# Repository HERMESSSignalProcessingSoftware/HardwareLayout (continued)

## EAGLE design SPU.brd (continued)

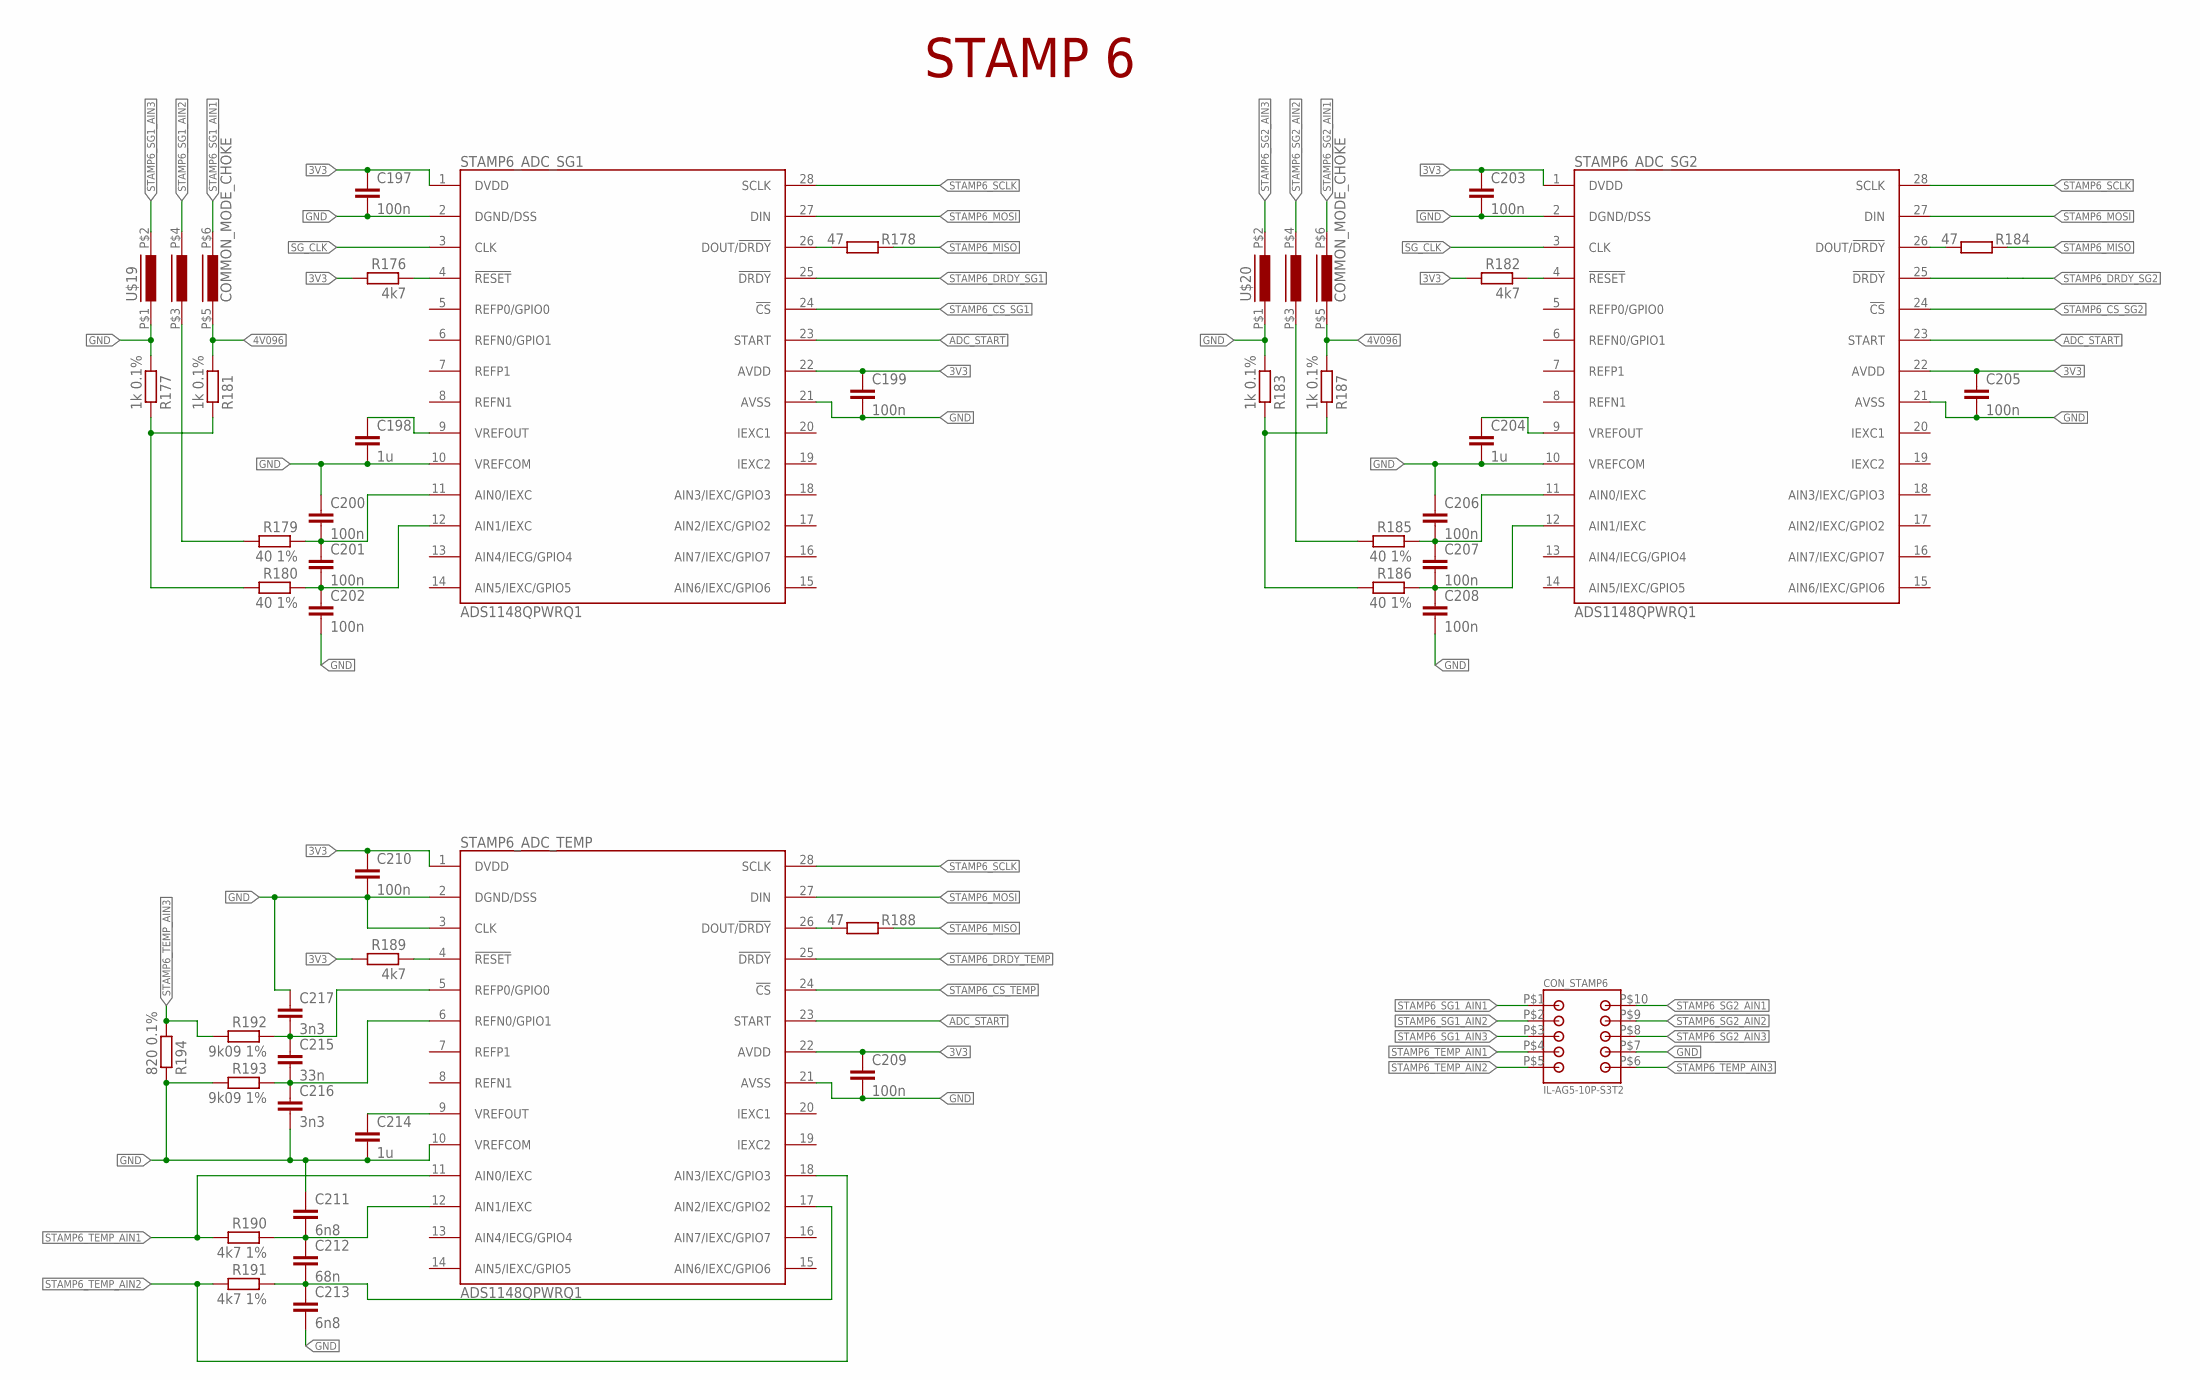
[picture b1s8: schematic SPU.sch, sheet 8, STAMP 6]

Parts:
C197, C199, C200, C201, C202, C203, C205, C206, C207, C208, C209, C210: 100n; C0805
C198, C204, C214: 1u; C0805
C211, C213: 6n8; C0805
C212: 68n; C0805
C215: 33n; C0805
C216, C217: 3n3; C0805
CON_STAMP6: IL-AG5-10P-S3T2
R176, R182, R189: 4k7; R0805
R177, R181, R183, R187: 1k 0.1%; R0805
R178, R184, R188: 47; R0805
R179, R180, R185, R186: 40 1%; R0805
R190, R191: 4k7 1%; R0805
R192, R193: 9k09 1%; R0805
R194: 820 0.1%; R0805
STAMP6_ADC_SG1, STAMP6_ADC_SG2, STAMP6_ADC_TEMP: ADS1148QPWRQ1; TSSOP28
U$19, U$20: COMMON_MODE_CHOKE

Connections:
3V3: C197.1, C199.1, C203.1, C205.1, C209.1, C210.1, R176.2, R182.2, R189.2, STAMP6_ADC_SG1.1 (DVDD), STAMP6_ADC_SG1.22 (AVDD), STAMP6_ADC_SG2.1 (DVDD), STAMP6_ADC_SG2.22 (AVDD), STAMP6_ADC_TEMP.1 (DVDD), STAMP6_ADC_TEMP.22 (AVDD); also elsewhere on the board
4V096: R181.2, R187.2, U$19.P$5 (5), U$20.P$5 (5); also elsewhere on the board
ADC_START: STAMP6_ADC_SG1.23 (START), STAMP6_ADC_SG2.23 (START), STAMP6_ADC_TEMP.23 (START); also elsewhere on the board
GND: C197.2, C198.2, C199.2, C200.1, C202.2, C203.2, C204.2, C205.2, C206.1, C208.2, C209.2, C210.2, C211.1, C213.2, C214.2, C216.2, C217.1, CON_STAMP6.P$7, R177.2, R183.2, R193.2, R194.1, STAMP6_ADC_SG1.2 (DGND/DSS), STAMP6_ADC_SG1.10 (VREFCOM), STAMP6_ADC_SG1.21 (AVSS), STAMP6_ADC_SG2.2 (DGND/DSS), STAMP6_ADC_SG2.10 (VREFCOM), STAMP6_ADC_SG2.21 (AVSS), STAMP6_ADC_TEMP.2 (DGND/DSS), STAMP6_ADC_TEMP.3 (CLK), STAMP6_ADC_TEMP.10 (VREFCOM), STAMP6_ADC_TEMP.21 (AVSS), U$19.P$1 (1), U$20.P$1 (1); also elsewhere on the board
unnamed: R176.1, STAMP6_ADC_SG1.4 (!RESET)
unnamed: C198.1, STAMP6_ADC_SG1.9 (VREFOUT)
unnamed: R178.2, STAMP6_ADC_SG1.26 (DOUT/!DRDY)
unnamed: C200.2, C201.1, R179.1, STAMP6_ADC_SG1.11 (AIN0/IEXC)
unnamed: C201.2, C202.1, R180.1, STAMP6_ADC_SG1.12 (AIN1/IEXC)
unnamed: R177.1, R180.2, R181.1
unnamed: R179.2, U$19.P$3 (3)
unnamed: R182.1, STAMP6_ADC_SG2.4 (!RESET)
unnamed: C204.1, STAMP6_ADC_SG2.9 (VREFOUT)
unnamed: R184.2, STAMP6_ADC_SG2.26 (DOUT/!DRDY)
unnamed: C206.2, C207.1, R185.1, STAMP6_ADC_SG2.11 (AIN0/IEXC)
unnamed: C207.2, C208.1, R186.1, STAMP6_ADC_SG2.12 (AIN1/IEXC)
unnamed: R183.1, R186.2, R187.1
unnamed: R185.2, U$20.P$3 (3)
unnamed: R188.2, STAMP6_ADC_TEMP.26 (DOUT/!DRDY)
unnamed: R189.1, STAMP6_ADC_TEMP.4 (!RESET)
unnamed: C211.2, C212.1, R190.1, STAMP6_ADC_TEMP.12 (AIN1/IEXC)
unnamed: C212.2, C213.1, R191.1, STAMP6_ADC_TEMP.17 (AIN2/IEXC/GPIO2)
unnamed: C214.1, STAMP6_ADC_TEMP.9 (VREFOUT)
unnamed: C215.2, C216.1, R193.1, STAMP6_ADC_TEMP.6 (REFN0/GPIO1)
unnamed: C215.1, C217.2, R192.1, STAMP6_ADC_TEMP.5 (REFP0/GPIO0)
SG_CLK: STAMP6_ADC_SG1.3 (CLK), STAMP6_ADC_SG2.3 (CLK); also elsewhere on the board
STAMP6_CS_SG1: STAMP6_ADC_SG1.24 (!CS); also elsewhere on the board
STAMP6_CS_SG2: STAMP6_ADC_SG2.24 (!CS); also elsewhere on the board
STAMP6_CS_TEMP: STAMP6_ADC_TEMP.24 (!CS); also elsewhere on the board
STAMP6_DRDY_SG1: STAMP6_ADC_SG1.25 (!DRDY); also elsewhere on the board
STAMP6_DRDY_SG2: STAMP6_ADC_SG2.25 (!DRDY); also elsewhere on the board
STAMP6_DRDY_TEMP: STAMP6_ADC_TEMP.25 (!DRDY); also elsewhere on the board
STAMP6_MISO: R178.1, R184.1, R188.1; also elsewhere on the board
STAMP6_MOSI: STAMP6_ADC_SG1.27 (DIN), STAMP6_ADC_SG2.27 (DIN), STAMP6_ADC_TEMP.27 (DIN); also elsewhere on the board
STAMP6_SCLK: STAMP6_ADC_SG1.28 (SCLK), STAMP6_ADC_SG2.28 (SCLK), STAMP6_ADC_TEMP.28 (SCLK); also elsewhere on the board
STAMP6_SG1_AIN1: CON_STAMP6.P$1, U$19.P$6 (6)
STAMP6_SG1_AIN2: CON_STAMP6.P$2, U$19.P$4 (4)
STAMP6_SG1_AIN3: CON_STAMP6.P$3, U$19.P$2 (2)
STAMP6_SG2_AIN1: CON_STAMP6.P$10, U$20.P$6 (6)
STAMP6_SG2_AIN2: CON_STAMP6.P$9, U$20.P$4 (4)
STAMP6_SG2_AIN3: CON_STAMP6.P$8, U$20.P$2 (2)
STAMP6_TEMP_AIN1: CON_STAMP6.P$4, R190.2, STAMP6_ADC_TEMP.11 (AIN0/IEXC)
STAMP6_TEMP_AIN2: CON_STAMP6.P$5, R191.2, STAMP6_ADC_TEMP.18 (AIN3/IEXC/GPIO3)
STAMP6_TEMP_AIN3: CON_STAMP6.P$6, R192.2, R194.2

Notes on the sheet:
STAMP 6

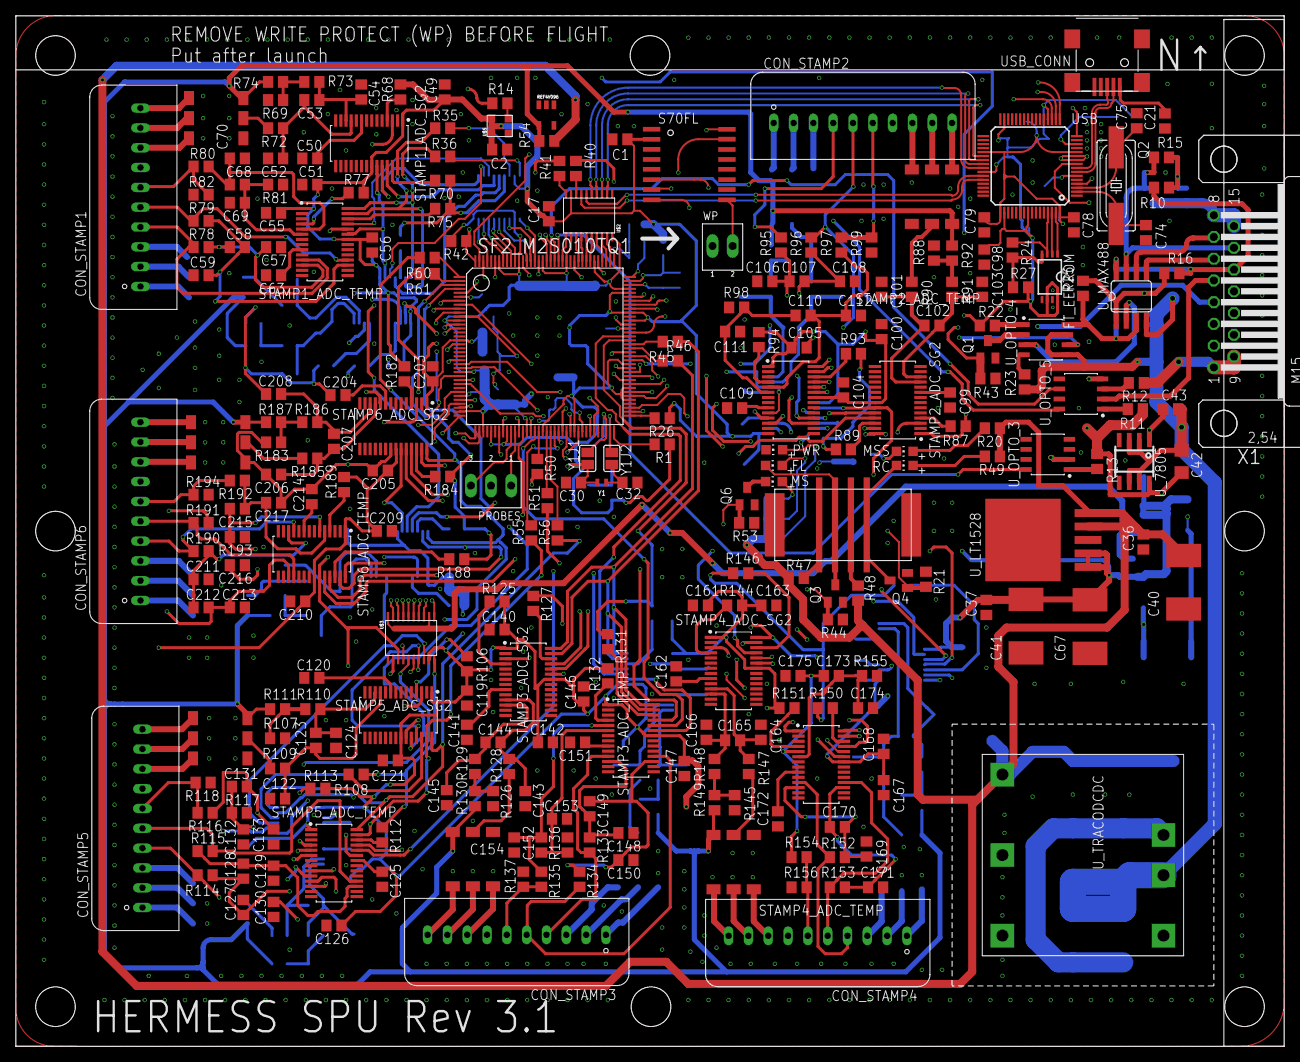
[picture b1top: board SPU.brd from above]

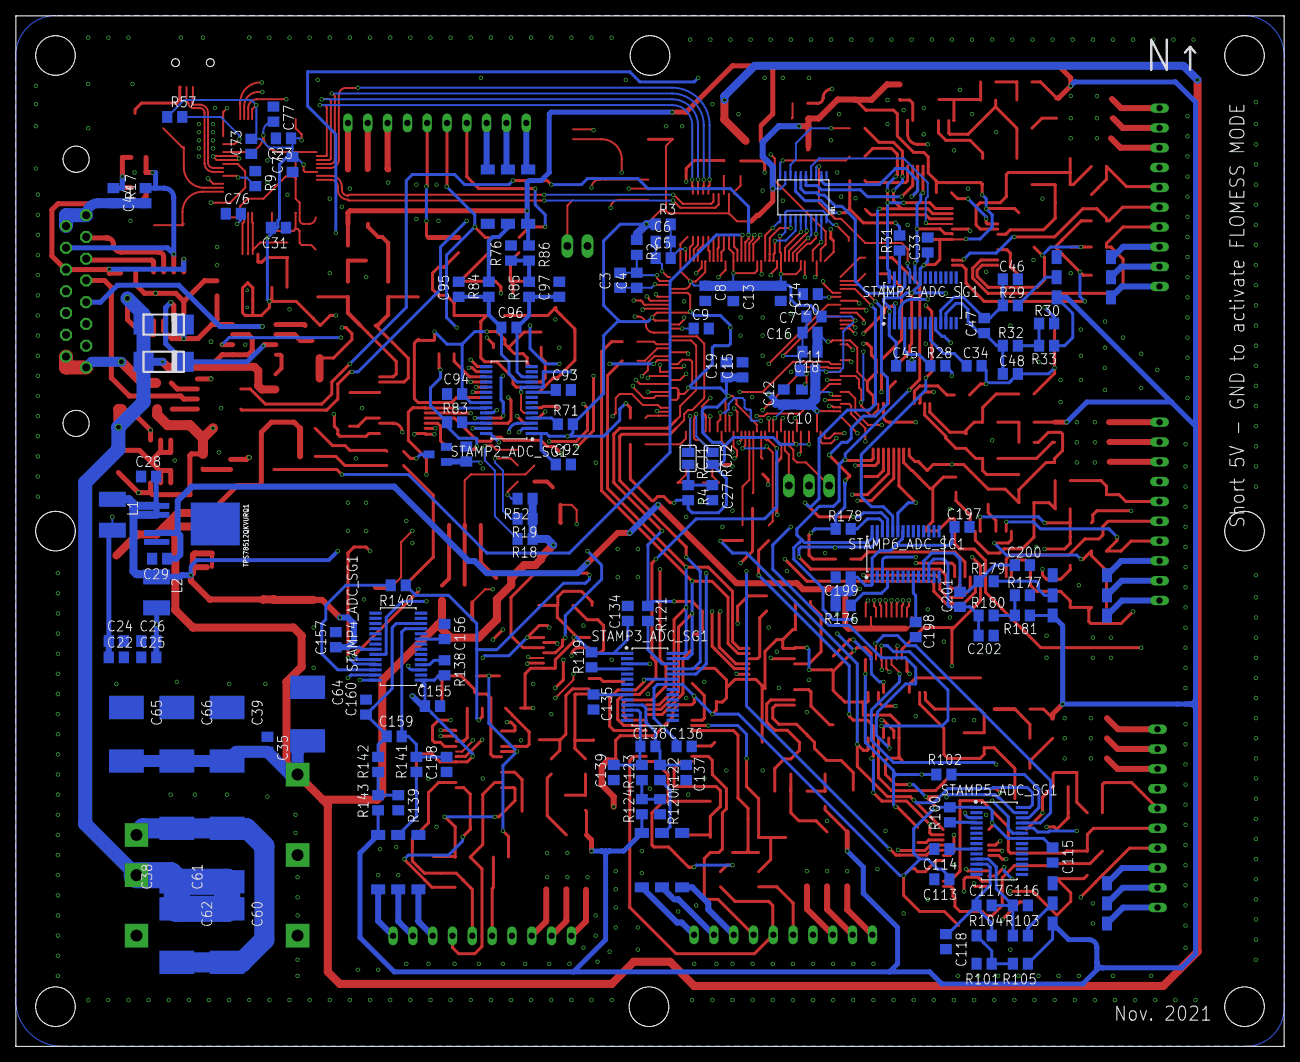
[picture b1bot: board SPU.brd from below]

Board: 4 copper layers, 160.0 x 130.0 mm, 421 parts (143 on the bottom side), 360 nets.

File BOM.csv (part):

"Qty";"Value";"Device";"Package";"Parts";"Description";"CATEGORY";"DESCRIPTION";"HEAT-SINK";"MANUFACTURER";"MF";"MPN";"OC_FARNELL";"OC_NEWARK";"OPERATING_TEMP";"OPERTAING_TEMP";"PART_STATUS";"POPULARITY";"ROHS_COMPLIANT";"SERIES";"SPICEPREFIX";"SUB-CATEGORY";"THERMALLOSS";"TYPE";"VALUE";
"2";"";"L-EUL1812";"L1812";"L1, L2";"INDUCTOR, European symbol";"";"";"";"";"";"";"";"";"";"";"";"18";"";"";"L";"";"";"";"";
"1";"";"M15H";"M15H";"X1";"SUB-D";"";"";"";"";"";"";"unknown";"unknown";"";"";"";"0";"";"";"";"";"";"";"";
"1";"";"PSS254_G2";"PSS254_G2";"WP";"";"";"";"";"";"";"";"";"";"";"";"";"";"";"";"";"";"";"";"";
"1";"";"PSS254_G3";"PSS254_G3";"PROBES";"";"";"";"";"";"";"";"";"";"";"";"";"";"";"";"";"";"";"";"";
"1";"";"USBMINIB";"USB-MINIB";"CN1";"USB Connectors";"";"";"";"";"";"";"";"";"";"";"";"";"";"";"";"";"";"";"";
"103";"100n";"C-EUC0805";"C0805";"C1, C7, C8, C9, C10, C11, C12, C13, C14, C15, C16, C17, C18, C19, C20, C21, C22, C23, C25, C28, C29, C30, C31, C32, C33, C35, C36, C37, C43, C45, C46, C47, C48, C49, C51, C52, C53, C54, C55, C56, C71, C72, C73, C92, C94, C95, C96, C97, C98, C100, C101, C102, C103, C104, C105, C113, C115, C116, C117, C118, C119, C121, C122, C123, C124, C125, C126, C134, C136, C137, C138, C139, C140, C142, C143, C144, C145, C146, C147, C155, C157, C158, C159, C160, C161, C163, C164, C165, C166, C167, C168, C197, C199, C200, C201, C202, C203, C205, C206, C207, C208, C209, C210";"CAPACITOR, European symbol";"";"";"";"";"";"";"";"";"";"";"";"88";"";"";"C";"";"";"";"";
"1";"100n";"C-EUC1206";"C1206";"C42";"CAPACITOR, European symbol";"";"";"";"";"";"";"";"";"";"";"";"54";"";"";"C";"";"";"";"";
"3";"10k";"R-EU_R0805";"R0805";"R1, R26, R27";"RESISTOR, European symbol";"";"";"";"";"";"";"";"";"";"";"";"86";"";"";"R";"";"";"";"";
"1";"10n";"C-EUC0805";"C0805";"C2";"CAPACITOR, European symbol";"";"";"";"";"";"";"";"";"";"";"";"88";"";"";"C";"";"";"";"";
"11";"10u";"CPOL-EUE/7260-38W";"E/7260-38W";"C38, C39, C40, C41, C60, C61, C62, C64, C65, C66, C67";"POLARIZED CAPACITOR, European symbol";"";"";"";"";"";"";"";"";"";"";"";"0";"";"";"C";"";"";"";"";
"1";"12MHz";"CRYSTALHC49UP";"HC49UP";"Q2";"CRYSTAL";"";"";"";"";"";"";"unknown";"unknown";"";"";"";"";"";"";"";"";"";"";"";
"1";"12k";"R-EU_R0805";"R0805";"R9";"RESISTOR, European symbol";"";"";"";"";"";"";"";"";"";"";"";"86";"";"";"R";"";"";"";"";
"1";"150n";"C-EUC0805";"C0805";"C27";"CAPACITOR, European symbol";"";"";"";"";"";"";"";"";"";"";"";"88";"";"";"C";"";"";"";"";
"5";"1V9";"LEDCHIP-LED0805";"CHIP-LED0805";"LED1, LED2, LED3, LED4, LED5";"LED";"";"";"";"";"";"";"";"";"";"";"";"";"";"";"";"";"";"";"";
"1";"1k";"R-EU_R0805";"R0805";"R57";"RESISTOR, European symbol";"";"";"";"";"";"";"";"";"";"";"";"86";"";"";"R";"";"";"";"";
"6";"1k";"R-EU_R0805";"R0805";"R21, R22, R34, R43, R44, R53";"RESISTOR, European symbol";"";"";"";"";"";"";"";"";"";"";"";"";"";"";"";"";"";"";"";
"24";"1k 0.1%";"R-EU_R0805";"R0805";"R30, R33, R69, R74, R76, R86, R88, R92, R101, R105, R107, R111, R120, R124, R126, R130, R139, R143, R145, R149, R177, R181, R183, R187";"RESISTOR, European symbol";"";"";"";"";"";"";"";"";"";"";"";"86";"";"";"R";"";"";"";"";
"18";"1u";"C-EUC0805";"C0805";"C34, C50, C63, C93, C99, C109, C114, C120, C130, C135, C141, C151, C156, C162, C172, C198, C204, C214";"CAPACITOR, European symbol";"";"";"";"";"";"";"";"";"";"";"";"88";"";"";"C";"";"";"";"";
"3";"2";"R-EU_R0805";"R0805";"R2, R3, R4";"RESISTOR, European symbol";"";"";"";"";"";"";"";"";"";"";"";"86";"";"";"R";"";"";"";"";
"2";"22p";"C-EUC0805";"C0805";"C74, C75";"CAPACITOR, European symbol";"";"";"";"";"";"";"";"";"";"";"";"88";"";"";"C";"";"";"";"";
"1";"2k2";"R-EU_R0805";"R0805";"R24";"RESISTOR, European symbol";"";"";"";"";"";"";"";"";"";"";"";"86";"";"";"R";"";"";"";"";
"2";"330";"R-EU_R0805";"R0805";"R47, R48";"RESISTOR, European symbol";"";"";"";"";"";"";"";"";"";"";"";"";"";"";"";"";"";"";"";
"6";"33n";"C-EUC0805";"C0805";"C68, C110, C131, C152, C173, C215";"CAPACITOR, European symbol";"";"";"";"";"";"";"";"";"";"";"";"88";"";"";"C";"";"";"";"";
"1";"3R65";"R-EU_R0805";"R0805";"R54";"RESISTOR, European symbol";"";"";"";"";"";"";"";"";"";"";"";"86";"";"";"R";"";"";"";"";
"4";"3k";"R-EU_R0805";"R0805";"R11, R12, R13, R23";"RESISTOR, European symbol";"";"";"";"";"";"";"";"";"";"";"";"";"";"";"";"";"";"";"";
"2";"3k3";"R-EU_R0805";"R0805";"R16, R17";"RESISTOR, European symbol";"";"";"";"";"";"";"";"";"";"";"";"";"";"";"";"";"";"";"";
"12";"3n3";"C-EUC0805";"C0805";"C69, C70, C111, C112, C132, C133, C153, C154, C174, C175, C216, C217";"CAPACITOR, European symbol";"";"";"";"";"";"";"";"";"";"";"";"88";"";"";"C";"";"";"";"";
"24";"40 1%";"R-EU_R0805";"R0805";"R29, R32, R72, R73, R84, R85, R90, R91, R103, R104, R109, R110, R122, R123, R128, R129, R141, R142, R147, R148, R179, R180, R185, R186";"RESISTOR, European symbol";"";"";"";"";"";"";"";"";"";"";"";"86";"";"";"R";"";"";"";"";
"31";"47";"R-EU_R0805";"R0805";"R14, R31, R35, R36, R40, R41, R45, R46, R50, R51, R55, R56, R60, R61, R70, R75, R83, R89, R93, R102, R108, R112, R121, R127, R131, R140, R146, R150, R178, R184, R188";"RESISTOR, European symbol";"";"";"";"";"";"";"";"";"";"";"";"86";"";"";"R";"";"";"";"";
"2";"470n";"C-EUC0805";"C0805";"C4, C6";"CAPACITOR, European symbol";"";"";"";"";"";"";"";"";"";"";"";"88";"";"";"C";"";"";"";"";
"18";"4k7";"R-EU_R0805";"R0805";"R28, R68, R71, R77, R87, R94, R100, R106, R113, R119, R125, R132, R138, R144, R151, R176, R182, R189";"RESISTOR, European symbol";"";"";"";"";"";"";"";"";"";"";"";"86";"";"";"R";"";"";"";"";
"12";"4k7 1%";"R-EU_R0805";"R0805";"R78, R79, R95, R96, R114, R115, R133, R134, R152, R153, R190, R191";"RESISTOR, European symbol";"";"";"";"";"";"";"";"";"";"";"";"86";"";"";"R";"";"";"";"";
"4";"4u7";"C-EUC0805";"C0805";"C3, C5, C24, C26";"CAPACITOR, European symbol";"";"";"";"";"";"";"";"";"";"";"";"88";"";"";"C";"";"";"";"";
"2";"500";"R-EU_R0805";"R0805";"R10, R15";"RESISTOR, European symbol";"";"";"";"";"";"";"";"";"";"";"";"";"";"";"";"";"";"";"";
"2";"5V6";"DZMELF";"DMELF";"D1, D5";"Zener diode";"";"";"";"";"";"";"";"";"";"";"";"";"";"";"";"";"";"";"";
"4";"600";"R-EU_R0805";"R0805";"R37, R38, R39, R42";"RESISTOR, European symbol";"";"";"";"";"";"";"";"";"";"";"";"86";"";"";"R";"";"";"";"";
"5";"680";"R-EU_R0805";"R0805";"R18, R19, R20, R49, R52";"RESISTOR, European symbol";"";"";"";"";"";"";"";"";"";"";"";"";"";"";"";"";"";"";"";
"6";"68n";"C-EUC0805";"C0805";"C58, C107, C128, C149, C170, C212";"CAPACITOR, European symbol";"";"";"";"";"";"";"";"";"";"";"";"88";"";"";"C";"";"";"";"";
"12";"6n8";"C-EUC0805";"C0805";"C57, C59, C106, C108, C127, C129, C148, C150, C169, C171, C211, C213";"CAPACITOR, European symbol";"";"";"";"";"";"";"";"";"";"";"";"88";"";"";"C";"";"";"";"";
"1";"7k5";"R-EU_R0805";"R0805";"R25";"RESISTOR, European symbol";"";"";"";"";"";"";"";"";"";"";"";"86";"";"";"R";"";"";"";"";
"6";"820 0.1%";"R-EU_R0805";"R0805";"R82, R99, R118, R137, R156, R194";"RESISTOR, European symbol";"";"";"";"";"";"";"";"";"";"";"";"86";"";"";"R";"";"";"";"";
"12";"9k09 1%";"R-EU_R0805";"R0805";"R80, R81, R97, R98, R116, R117, R135, R136, R154, R155, R192, R193";"RESISTOR, European symbol";"";"";"";"";"";"";"";"";"";"";"";"86";"";"";"R";"";"";"";"";
"18";"ADS1148QPWRQ1";"ADS1148QPWRQ1";"TSSOP28";"STAMP1_ADC_SG1, STAMP1_ADC_SG2, STAMP1_ADC_SG5, STAMP1_ADC_SG6, STAMP1_ADC_SG7, STAMP1_ADC_SG8, STAMP1_ADC_SG9, STAMP1_ADC_SG10, STAMP1_ADC_SG11, STAMP1_ADC_SG12, STAMP1_ADC_SG15, STAMP1_ADC_SG16, STAMP1_ADC_TEMP, STAMP1_ADC_TEMP2, STAMP1_ADC_TEMP3, STAMP1_ADC_TEMP4, STAMP1_ADC_TEMP5, STAMP1_ADC_TEMP7";"";"";"";"";"";"";"";"";"";"";"";"";"";"";"";"";"";"";"";"";
"5";"BSS123";"BSS123";"SOT23";"Q1, Q3, Q4, Q5, Q6";"N-CHANNEL MOS FET";"";"";"";"";"";"";"";"";"";"";"";"21";"";"";"";"";"";"";"";
"12";"COMMON_MODE_CHOKE";"COMMON_MODE_CHOKE";"COMMON_MODE_CHOKE";"U$6, U$7, U$9, U$10, U$11, U$12, U$13, U$14, U$15, U$16, U$19, U$20";"WE-SL3 SMT COMMON MODE LINE FILT";"";"";"";"";"";"";"";"";"";"";"";"";"";"";"";"";"";"";"";
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
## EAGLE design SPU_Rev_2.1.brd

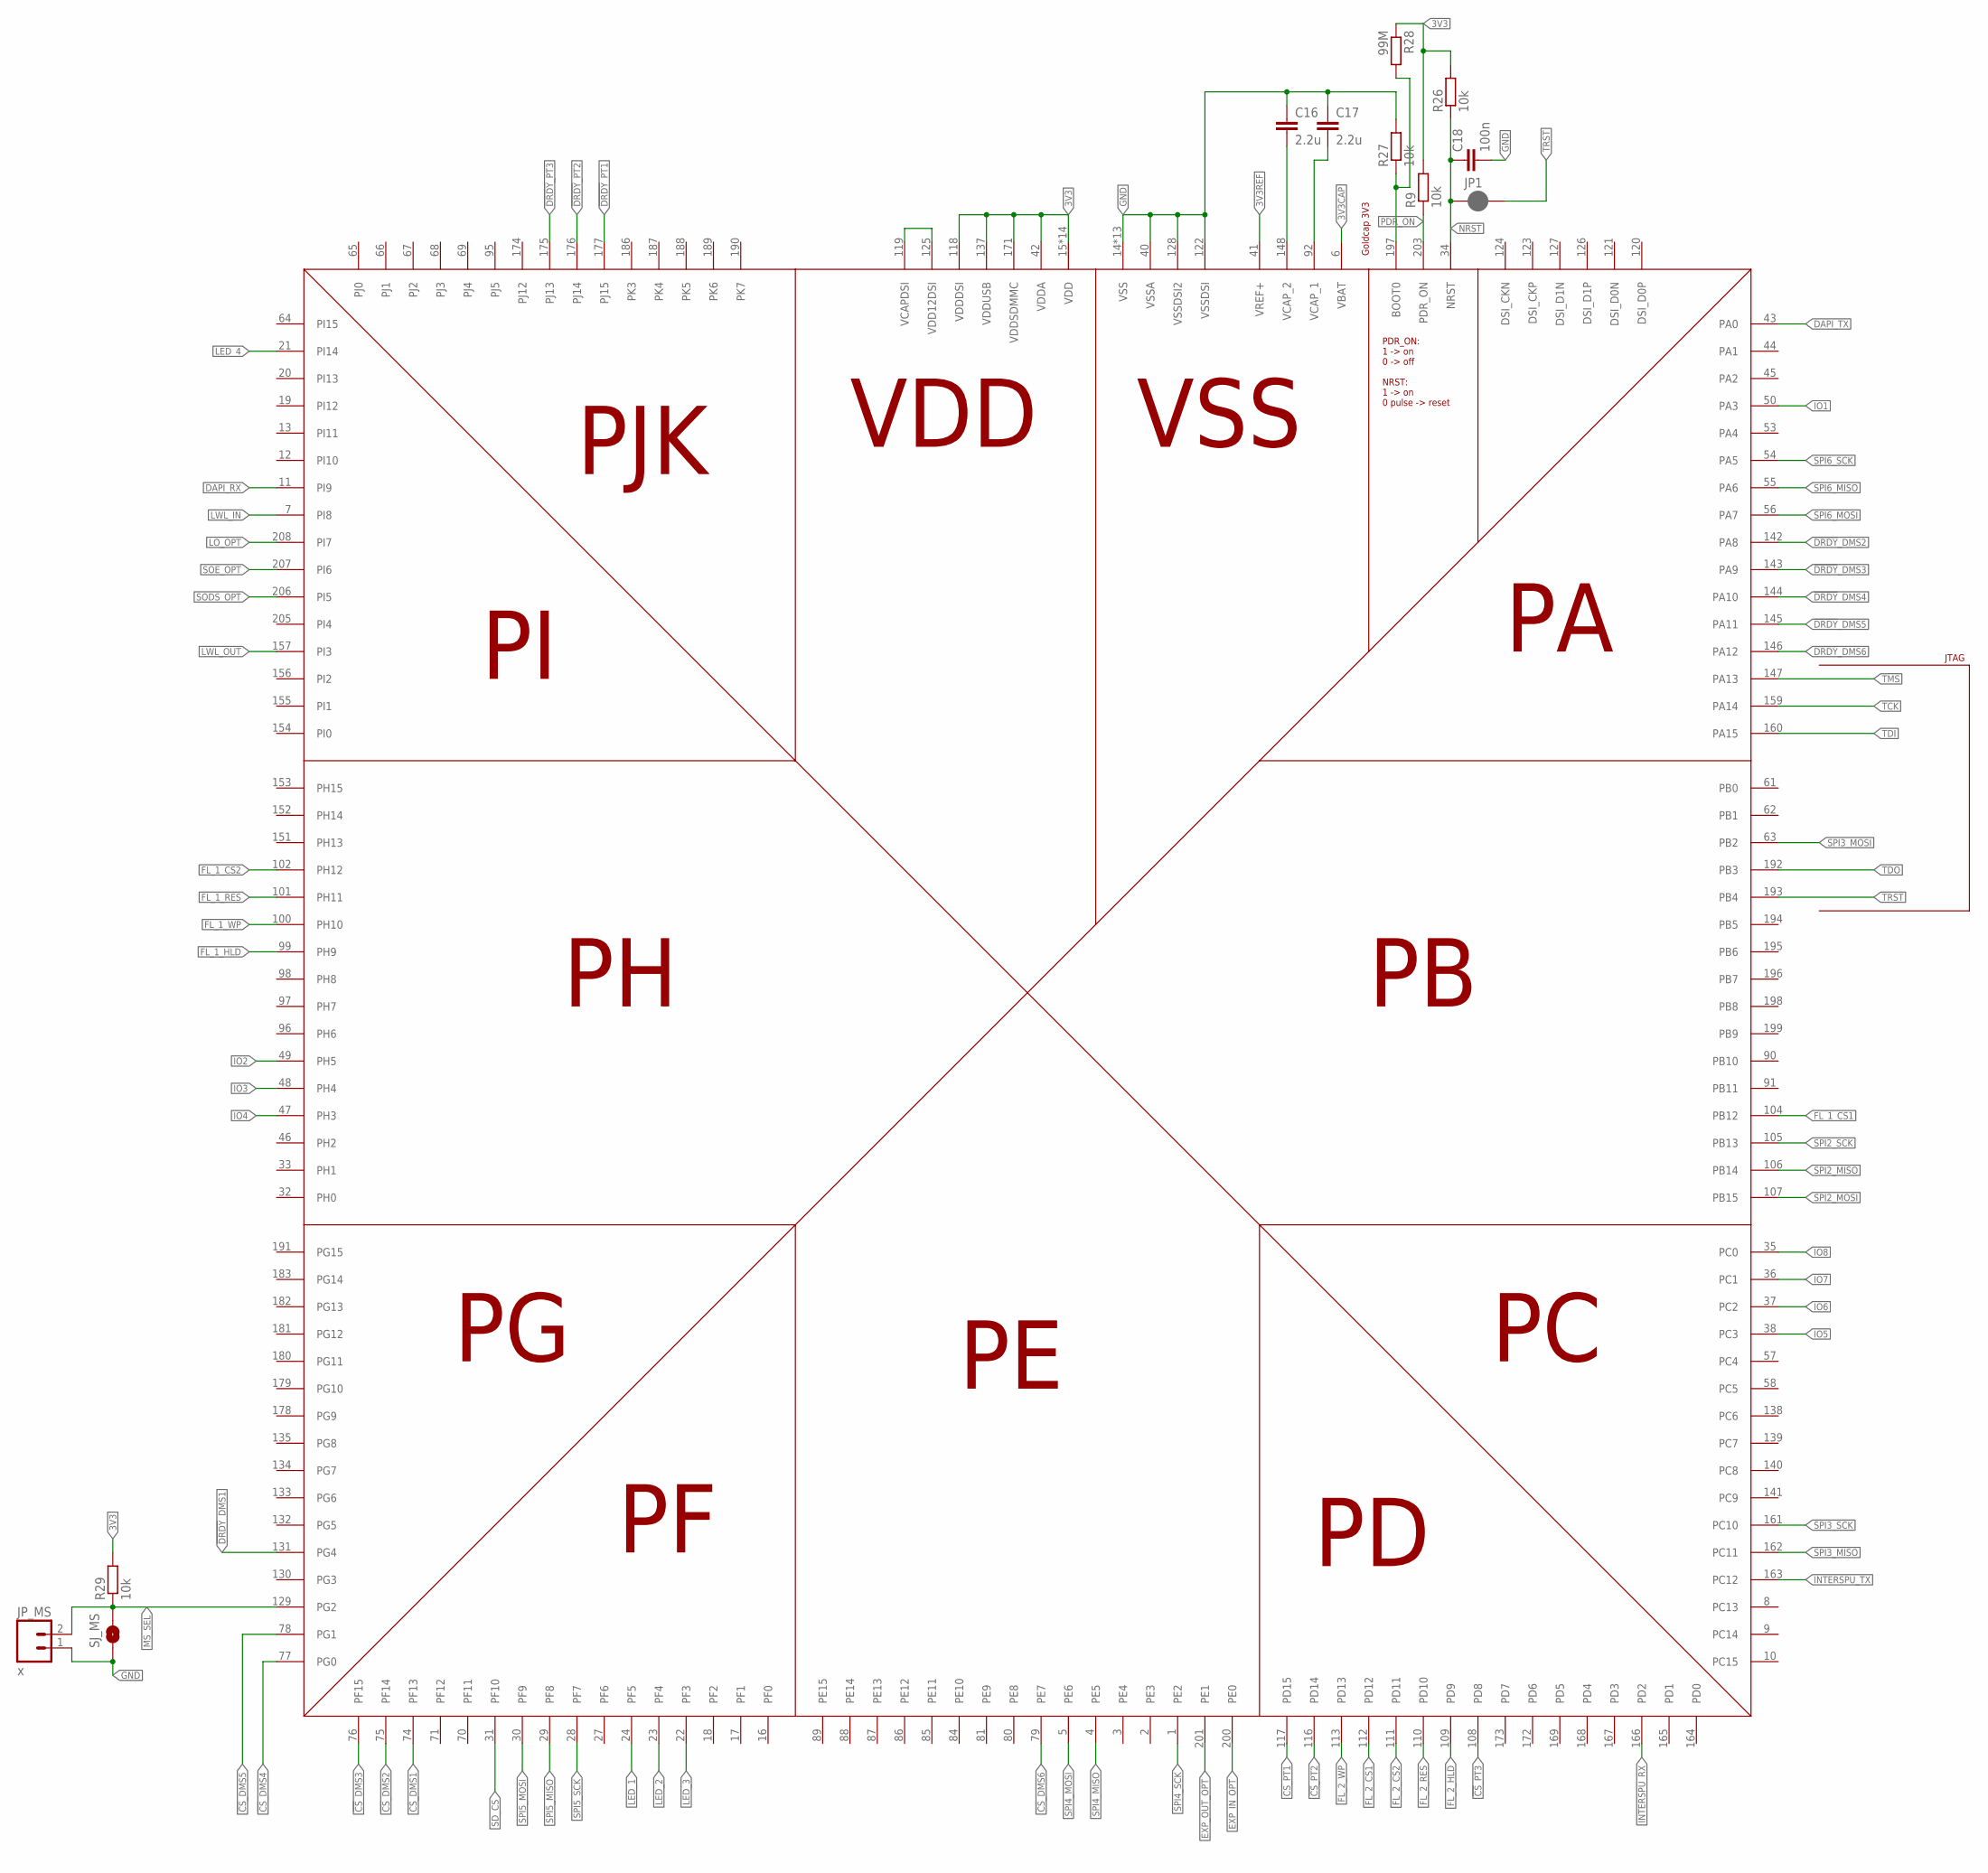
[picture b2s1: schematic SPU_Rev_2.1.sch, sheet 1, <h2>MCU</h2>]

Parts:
C16, C17: 2.2u; C1206
C18: 100n; 0603-CAP
JP1: JUMPER-SMT_2_NC_PASTE_SILK; SMT-JUMPER_2_NC_PASTE_SILK
JP_MS: x; 1X02
R9, R26, R27, R29: 10k; R0805
R28: 99M; R0805
SJ_MS: SOLDERJUMPERNO; SJ_2S-NO
U_STM32F779: STM32F77XXXLQFP208; QFP50P3060X3060X385-208

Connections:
3V3: R9.2, R26.2, R28.1, R29.2, U_STM32F779.15 (VDD), U_STM32F779.26 (VDD), U_STM32F779.39 (VDD), U_STM32F779.42 (VDDA), U_STM32F779.52 (VDD), U_STM32F779.59 (VDD), U_STM32F779.73 (VDD), U_STM32F779.83 (VDD), U_STM32F779.94 (VDD), U_STM32F779.103 (VDD), U_STM32F779.115 (VDD), U_STM32F779.118 (VDDDSI), U_STM32F779.137 (VDDUSB), U_STM32F779.150 (VDD), U_STM32F779.158 (VDD), U_STM32F779.171 (VDDSDMMC), U_STM32F779.185 (VDD), U_STM32F779.204 (VDD); also elsewhere on the board
3V3CAP: U_STM32F779.6 (VBAT)
3V3REF: U_STM32F779.41 (VREF+); also elsewhere on the board
!CS!_DMS1: U_STM32F779.74 (PF13); also elsewhere on the board
!CS!_DMS2: U_STM32F779.75 (PF14); also elsewhere on the board
!CS!_DMS3: U_STM32F779.76 (PF15); also elsewhere on the board
!CS!_DMS4: U_STM32F779.77 (PG0); also elsewhere on the board
!CS!_DMS5: U_STM32F779.78 (PG1); also elsewhere on the board
!CS!_DMS6: U_STM32F779.79 (PE7); also elsewhere on the board
!CS!_PT1: U_STM32F779.117 (PD15); also elsewhere on the board
!CS!_PT2: U_STM32F779.116 (PD14); also elsewhere on the board
!CS!_PT3: U_STM32F779.108 (PD8); also elsewhere on the board
!DRDY!_DMS1: U_STM32F779.131 (PG4); also elsewhere on the board
!DRDY!_DMS2: U_STM32F779.142 (PA8); also elsewhere on the board
!DRDY!_DMS3: U_STM32F779.143 (PA9); also elsewhere on the board
!DRDY!_DMS4: U_STM32F779.144 (PA10); also elsewhere on the board
!DRDY!_DMS5: U_STM32F779.145 (PA11); also elsewhere on the board
!DRDY!_DMS6: U_STM32F779.146 (PA12); also elsewhere on the board
!DRDY!_PT1: U_STM32F779.177 (PJ15); also elsewhere on the board
!DRDY!_PT2: U_STM32F779.176 (PJ14); also elsewhere on the board
!DRDY!_PT3: U_STM32F779.175 (PJ13); also elsewhere on the board
DAPI_RX: U_STM32F779.11 (PI9); also elsewhere on the board
DAPI_TX: U_STM32F779.43 (PA0); also elsewhere on the board
EXP_IN_OPT: U_STM32F779.200 (PE0); also elsewhere on the board
EXP_OUT_OPT: U_STM32F779.201 (PE1); also elsewhere on the board
FL_1_CS1: U_STM32F779.104 (PB12); also elsewhere on the board
FL_1_CS2: U_STM32F779.102 (PH12); also elsewhere on the board
FL_1_HLD: U_STM32F779.99 (PH9); also elsewhere on the board
FL_1_RES: U_STM32F779.101 (PH11); also elsewhere on the board
FL_1_WP: U_STM32F779.100 (PH10); also elsewhere on the board
FL_2_CS1: U_STM32F779.112 (PD12); also elsewhere on the board
FL_2_CS2: U_STM32F779.111 (PD11); also elsewhere on the board
FL_2_HLD: U_STM32F779.109 (PD9); also elsewhere on the board
FL_2_RES: U_STM32F779.110 (PD10); also elsewhere on the board
FL_2_WP: U_STM32F779.113 (PD13); also elsewhere on the board
GND: C16.1, C17.1, C18.2, JP_MS.1, R27.2, SJ_MS.1, U_STM32F779.14 (VSS), U_STM32F779.25 (VSS), U_STM32F779.40 (VSSA), U_STM32F779.51 (VSS), U_STM32F779.60 (VSS), U_STM32F779.72 (VSS), U_STM32F779.82 (VSS), U_STM32F779.93 (VSS), U_STM32F779.114 (VSS), U_STM32F779.122 (VSSDSI), U_STM32F779.128 (VSSDSI2), U_STM32F779.136 (VSS), U_STM32F779.149 (VSS), U_STM32F779.170 (VSS), U_STM32F779.184 (VSS), U_STM32F779.202 (VSS); also elsewhere on the board
INTERSPU_RX: U_STM32F779.166 (PD2); also elsewhere on the board
INTERSPU_TX: U_STM32F779.163 (PC12); also elsewhere on the board
IO1: U_STM32F779.50 (PA3); also elsewhere on the board
IO2: U_STM32F779.49 (PH5); also elsewhere on the board
IO3: U_STM32F779.48 (PH4); also elsewhere on the board
IO4: U_STM32F779.47 (PH3); also elsewhere on the board
IO5: U_STM32F779.38 (PC3); also elsewhere on the board
IO6: U_STM32F779.37 (PC2); also elsewhere on the board
IO7: U_STM32F779.36 (PC1); also elsewhere on the board
IO8: U_STM32F779.35 (PC0); also elsewhere on the board
LED_1: U_STM32F779.24 (PF5); also elsewhere on the board
LED_2: U_STM32F779.23 (PF4); also elsewhere on the board
LED_3: U_STM32F779.22 (PF3); also elsewhere on the board
LED_4: U_STM32F779.21 (PI14); also elsewhere on the board
LO_OPT: U_STM32F779.208 (PI7); also elsewhere on the board
LWL_IN: U_STM32F779.7 (PI8); also elsewhere on the board
LWL_OUT: U_STM32F779.157 (PI3); also elsewhere on the board
MS_SEL: JP_MS.2, R29.1, SJ_MS.2, U_STM32F779.129 (PG2)
unnamed: C16.2, U_STM32F779.148 (VCAP_2)
unnamed: C17.2, U_STM32F779.92 (VCAP_1)
unnamed: U_STM32F779.119 (VCAPDSI), U_STM32F779.125 (VDD12DSI)
unnamed: R27.1, R28.2, U_STM32F779.197 (BOOT0)
NRST: C18.1, JP1.1, R26.1, U_STM32F779.34 (NRST); also elsewhere on the board
PDR_ON: R9.1, U_STM32F779.203 (PDR_ON)
SD_CS: U_STM32F779.31 (PF10); also elsewhere on the board
SODS_OPT: U_STM32F779.206 (PI5); also elsewhere on the board
SOE_OPT: U_STM32F779.207 (PI6); also elsewhere on the board
SPI2_MISO: U_STM32F779.106 (PB14); also elsewhere on the board
SPI2_MOSI: U_STM32F779.107 (PB15); also elsewhere on the board
SPI2_SCK: U_STM32F779.105 (PB13); also elsewhere on the board
SPI3_MISO: U_STM32F779.162 (PC11); also elsewhere on the board
SPI3_MOSI: U_STM32F779.63 (PB2); also elsewhere on the board
SPI3_SCK: U_STM32F779.161 (PC10); also elsewhere on the board
SPI4_MISO: U_STM32F779.4 (PE5); also elsewhere on the board
SPI4_MOSI: U_STM32F779.5 (PE6); also elsewhere on the board
SPI4_SCK: U_STM32F779.1 (PE2); also elsewhere on the board
SPI5_MISO: U_STM32F779.29 (PF8); also elsewhere on the board
SPI5_MOSI: U_STM32F779.30 (PF9); also elsewhere on the board
SPI5_SCK: U_STM32F779.28 (PF7); also elsewhere on the board
SPI6_MISO: U_STM32F779.55 (PA6); also elsewhere on the board
SPI6_MOSI: U_STM32F779.56 (PA7); also elsewhere on the board
SPI6_SCK: U_STM32F779.54 (PA5); also elsewhere on the board
TCK: U_STM32F779.159 (PA14); also elsewhere on the board
TDI: U_STM32F779.160 (PA15); also elsewhere on the board
TDO: U_STM32F779.192 (PB3); also elsewhere on the board
TMS: U_STM32F779.147 (PA13); also elsewhere on the board
TRST: JP1.2, U_STM32F779.193 (PB4); also elsewhere on the board

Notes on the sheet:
JTAG
Goldcap 3V3
PDR_ON: 1 -> on 0 -> off NRST: 1 -> on 0 pulse -> reset
